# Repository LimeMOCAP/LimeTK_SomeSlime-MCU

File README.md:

# LimeTK_SomeSlime-MCU

LimeTK_SomeSlime 是 SlimeVR 的一套硬件设计，但只有 PCB 部分没有外壳。

它是 LimeTK 项目中产生的一个副产品，它的上游是 `LimeTK_Soda-MCU v1.2` 但由于 ESP-IDF 对新手过于的不友好导致它的固件编写停滞了很久很久。\
SomeSlime-MCU 顾名思义（指 Slime）是一个 SlimeVR 的硬件设计方案，所以并不使用自定义的固件或者特别的 SlimeVR 固件分支，照常修改配置文件即可

也是因此这个项目有着不少 Soda 上残存的怨念，所以它的版本号永远都会以 `v0.` 开头

## 硬件设计理念

它们的理念都是尽可能的实现：最小的空间占用，以及可管控的电池安全

对此 LimeTK_SomeSlime 使用了 ESP32-C3 模组而非完整的开发板作为通讯模块。\
对于电池... 自己插根 JST-PH 的线上去，我不管啦（坏笑）。而且如果你想的话，板子上有三个接口可供菊花链哦

## PCB 制造

下载发布版本中的 `.zip` 或者带有 `gerber` 字样的压缩文件并提交到制造商即可，或者也可以检出对应的 git 标签用 kicad 打开项目从头导出一份 gerber 文件。\
至于导出标准嘛...

## 固件配置

文档位于: [docs/Firmware-example.md](docs/Firmware-example.md)

## 共享许可

硬件设计: CERN-OHL-W v2\
CERN Open Hardware Licence - weakly reciprocal - version 2

文档许可: CC BY 4.0\
知识共享许可协议 - 署名 4.0 国际

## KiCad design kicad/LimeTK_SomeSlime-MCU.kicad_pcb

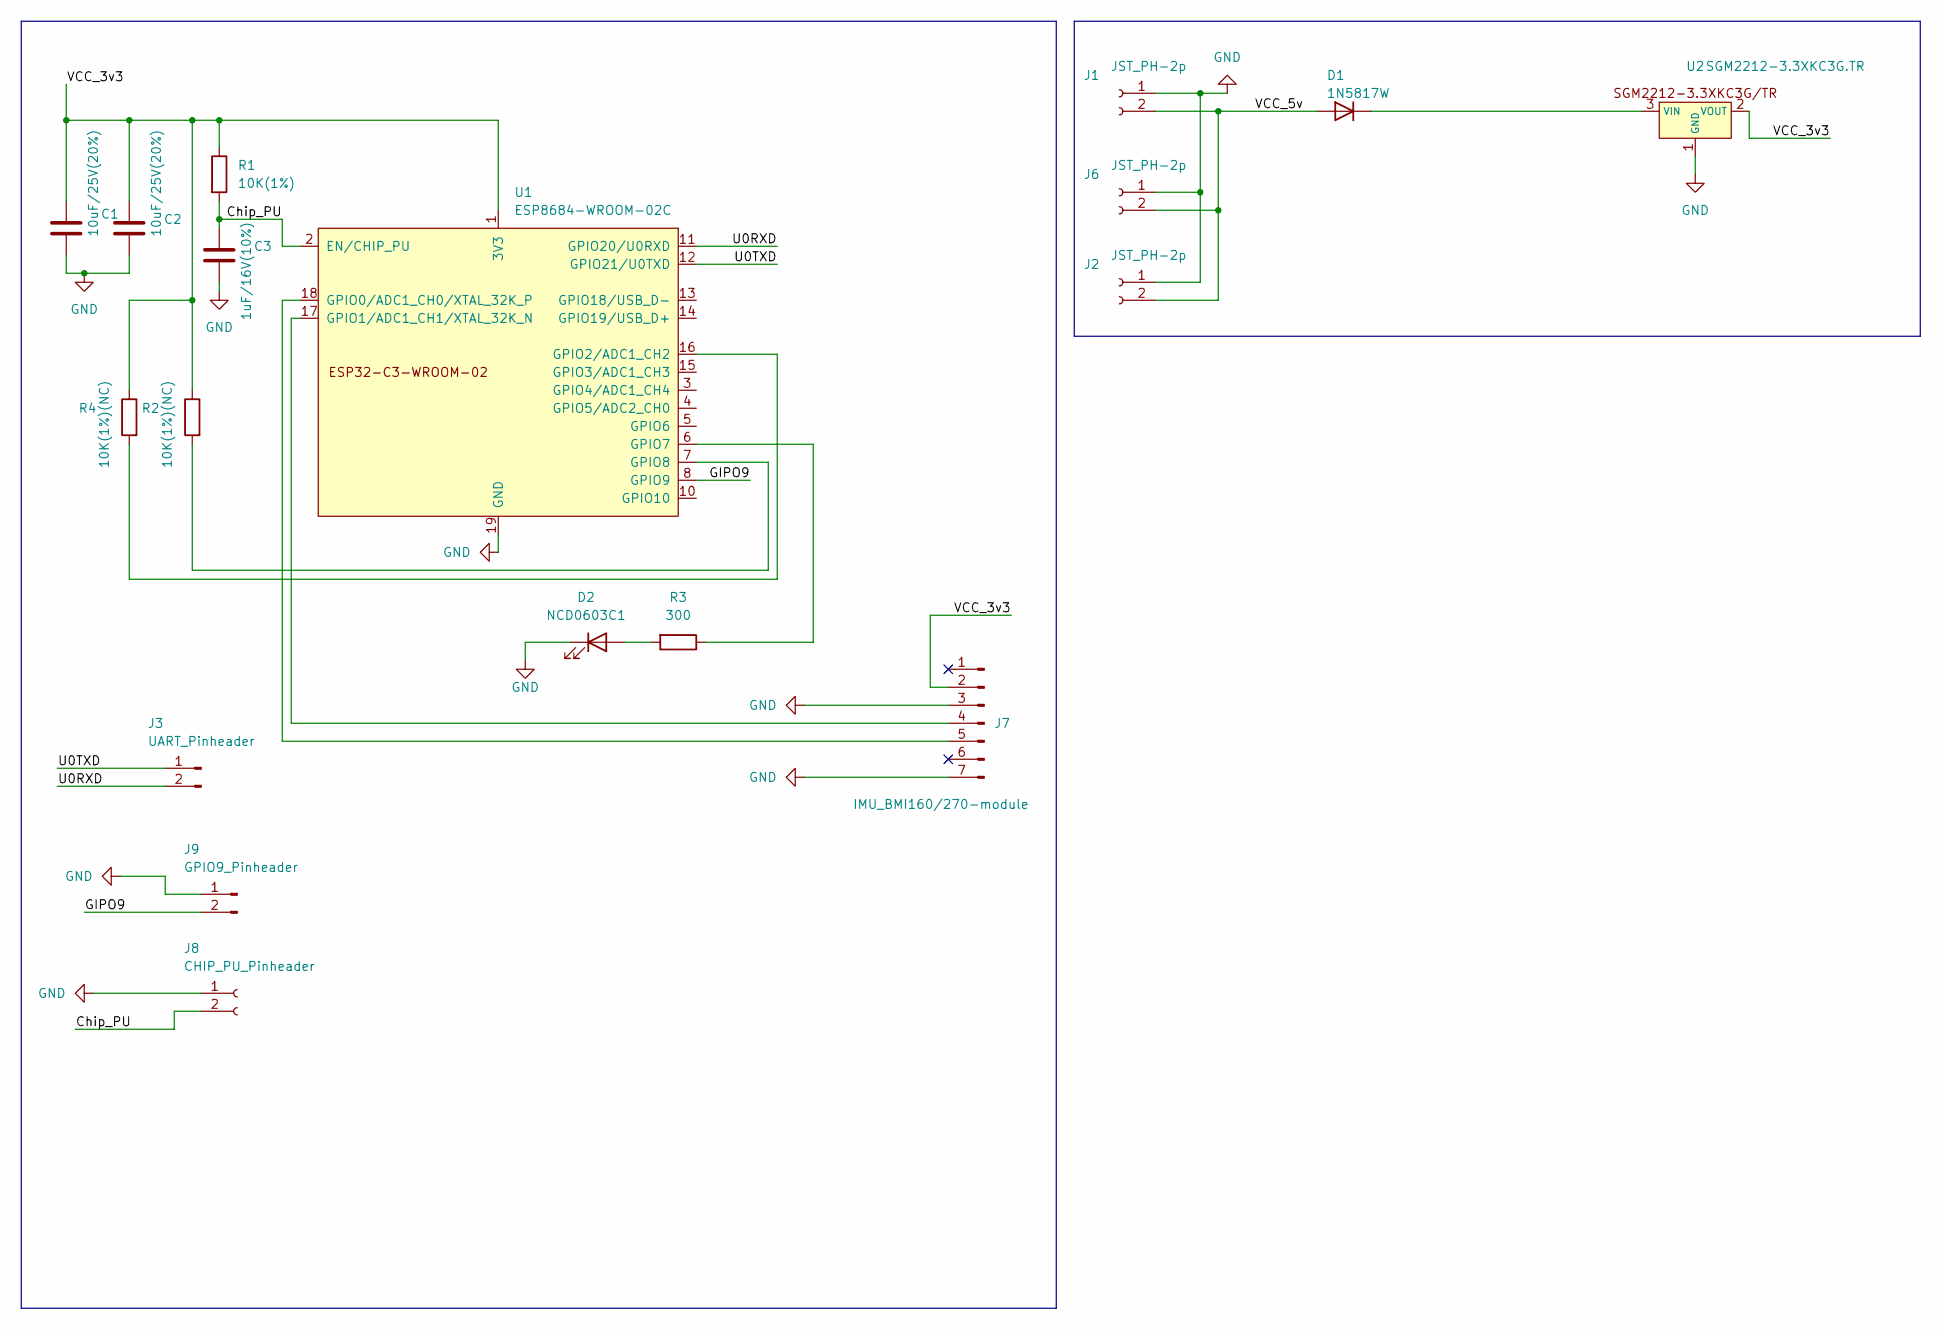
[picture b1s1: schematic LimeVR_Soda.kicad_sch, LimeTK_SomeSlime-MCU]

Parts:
C1, C2: 10uF/25V(20%); R_0603_1608Metric_Pad0.98x0.95mm_HandSolder
C3: 1uF/16V(10%); R_0603_1608Metric_Pad0.98x0.95mm_HandSolder
D1: 1N5817W; D_SOD-123
D2: NCD0603C1; LED_0603_1608Metric_Pad1.05x0.95mm_HandSolder
J1, J2, J6: JST_PH-2p; JST_PH_B2B-PH-K_1x02_P2.00mm_Vertical
J3: UART_Pinheader; PinHeader_1x02_P2.54mm_Vertical
J7: IMU_BMI160/270-module; PinHeader_1x07_P2.54mm_Vertical
J8: CHIP_PU_Pinheader; PinHeader_1x02_P2.54mm_Vertical
J9: GPIO9_Pinheader; PinHeader_1x02_P2.54mm_Vertical
R1: 10K(1%); R_0603_1608Metric_Pad0.98x0.95mm_HandSolder
R2, R4: 10K(1%)(NC); R_0603_1608Metric_Pad0.98x0.95mm_HandSolder
R3: 300; R_0603_1608Metric_Pad0.98x0.95mm_HandSolder
U1: ESP8684-WROOM-02C; ESP32-C3-WROOM-02
U2: SGM2212-3.3XKC3G.TR

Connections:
/Chip_PU: C3.1, J8.2, R1.2, U1.2 (EN/CHIP_PU)
/GIPO9: J9.2, U1.8 (GPIO9)
/U0RXD: J3.2, U1.11 (GPIO20/U0RXD)
/U0TXD: J3.1, U1.12 (GPIO21/U0TXD)
/VCC_3v3: C1.1, C2.1, J7.2, R1.1, R2.1, R4.1, U1.1 (3V3), U2.2 (VOUT)
/VCC_5v: D1.2 (A), J1.2, J2.2, J6.2
GND: C1.2, C2.2, C3.2, D2.1 (K), J1.1, J2.1, J6.1, J7.3, J7.7, J8.1, J9.1, U1.9 (GND), U1.19 (GND), U2.1 (GND)
unnamed: D1.1 (K), U2.3 (VIN)
unnamed: D2.2 (A), R3.2
unnamed: J7.4, U1.17 (GPIO1/ADC1_CH1/XTAL_32K_N)
unnamed: J7.5, U1.18 (GPIO0/ADC1_CH0/XTAL_32K_P)
unnamed: R4.2, U1.16 (GPIO2/ADC1_CH2)
unnamed: R3.1, U1.6 (GPIO7)
unnamed: R2.2, U1.7 (GPIO8)

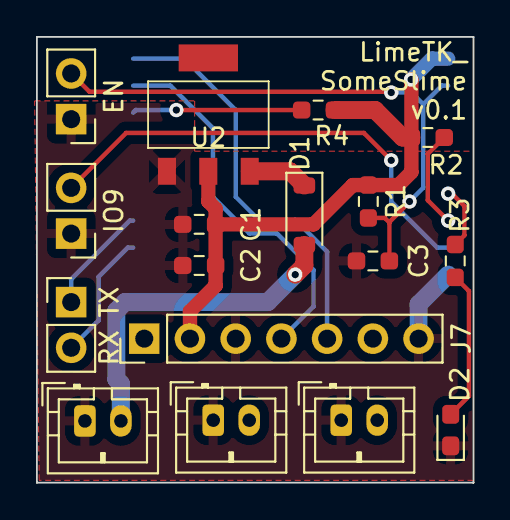
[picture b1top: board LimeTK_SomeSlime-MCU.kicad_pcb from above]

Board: 2 copper layers, 24.3 x 24.8 mm, 18 parts (1 on the bottom side), 14 nets.

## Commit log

2024-03-13 初始化储存库
2024-03-13 v0.1 Released
2024-03-13 更正文件名
    都是基于 soda 改得嘛，忘改名字了
2024-05-12 修改目录名
2024-05-12 添加固件参考文档
2024-05-12 完善文档
2024-05-12 修改许可描述
2024-05-12 修改文档
2024-05-13 更新自述文件
